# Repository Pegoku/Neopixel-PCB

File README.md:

# Neopixel-PCB
Neopixel matrix PCB made with kicad.

PS: my first PCB

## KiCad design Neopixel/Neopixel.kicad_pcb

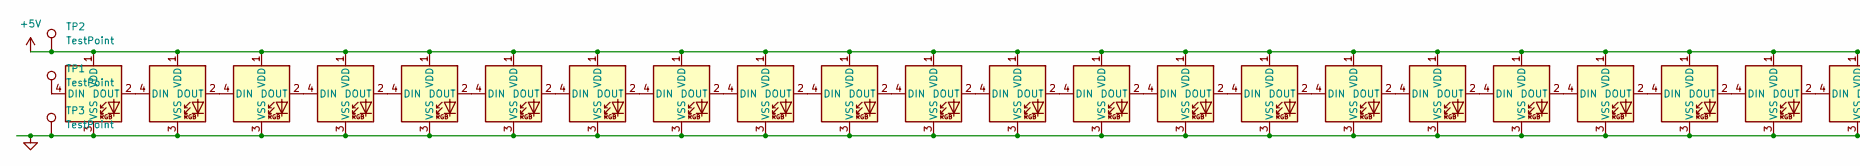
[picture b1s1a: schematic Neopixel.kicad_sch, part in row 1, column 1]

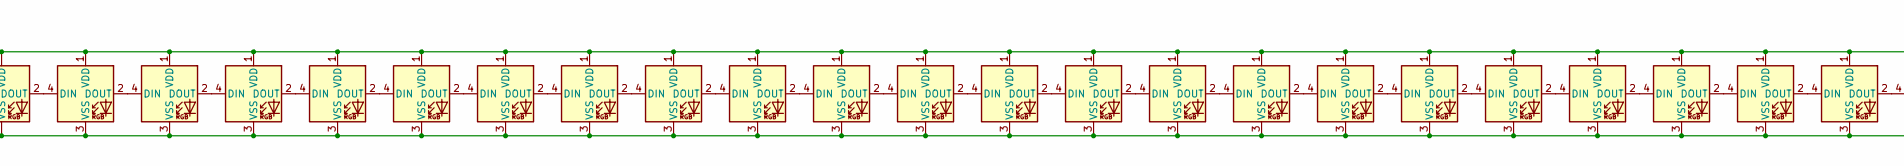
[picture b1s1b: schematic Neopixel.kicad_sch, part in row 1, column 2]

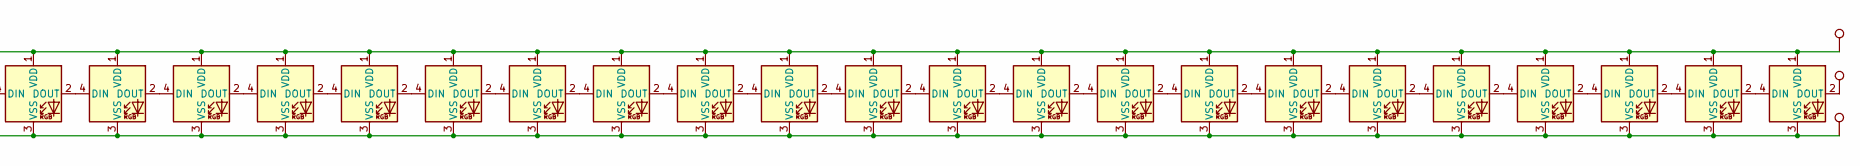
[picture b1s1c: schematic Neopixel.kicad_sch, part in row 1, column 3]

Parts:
D1, D2, D3, D4, D5, D6, D7, D8, D9, D10, D11, D12, D13, D14, D15, D16, D17, D18, D19, D20, D21, D22, D23, D24, D25, D26, D27, D28, D29, D30, D31, D32, D33, D34, D35, D36, D37, D38, D39, D40, D41, D42, D43, D44, D45, D46, D47, D48, D49, D50, D51, D52, D53, D54, D55, D56, D57, D58, D59, D60, D61, D62, D63, D64: WS2812B; LED_WS2812B_PLCC4_5.0x5.0mm_P3.2mm
TP1, TP2, TP3, TP4, TP5, TP6: TestPoint

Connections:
+5V: D1.1 (VDD), D2.1 (VDD), D3.1 (VDD), D4.1 (VDD), D5.1 (VDD), D6.1 (VDD), D7.1 (VDD), D8.1 (VDD), D9.1 (VDD), D10.1 (VDD), D11.1 (VDD), D12.1 (VDD), D13.1 (VDD), D14.1 (VDD), D15.1 (VDD), D16.1 (VDD), D17.1 (VDD), D18.1 (VDD), D19.1 (VDD), D20.1 (VDD), D21.1 (VDD), D22.1 (VDD), D23.1 (VDD), D24.1 (VDD), D25.1 (VDD), D26.1 (VDD), D27.1 (VDD), D28.1 (VDD), D29.1 (VDD), D30.1 (VDD), D31.1 (VDD), D32.1 (VDD), D33.1 (VDD), D34.1 (VDD), D35.1 (VDD), D36.1 (VDD), D37.1 (VDD), D38.1 (VDD), D39.1 (VDD), D40.1 (VDD), D41.1 (VDD), D42.1 (VDD), D43.1 (VDD), D44.1 (VDD), D45.1 (VDD), D46.1 (VDD), D47.1 (VDD), D48.1 (VDD), D49.1 (VDD), D50.1 (VDD), D51.1 (VDD), D52.1 (VDD), D53.1 (VDD), D54.1 (VDD), D55.1 (VDD), D56.1 (VDD), D57.1 (VDD), D58.1 (VDD), D59.1 (VDD), D60.1 (VDD), D61.1 (VDD), D62.1 (VDD), D63.1 (VDD), D64.1 (VDD), TP2.1, TP5.1; also elsewhere on the board
GND: D1.3 (VSS), D2.3 (VSS), D3.3 (VSS), D4.3 (VSS), D5.3 (VSS), D6.3 (VSS), D7.3 (VSS), D8.3 (VSS), D9.3 (VSS), D10.3 (VSS), D11.3 (VSS), D12.3 (VSS), D13.3 (VSS), D14.3 (VSS), D15.3 (VSS), D16.3 (VSS), D17.3 (VSS), D18.3 (VSS), D19.3 (VSS), D20.3 (VSS), D21.3 (VSS), D22.3 (VSS), D23.3 (VSS), D24.3 (VSS), D25.3 (VSS), D26.3 (VSS), D27.3 (VSS), D28.3 (VSS), D29.3 (VSS), D30.3 (VSS), D31.3 (VSS), D32.3 (VSS), D33.3 (VSS), D34.3 (VSS), D35.3 (VSS), D36.3 (VSS), D37.3 (VSS), D38.3 (VSS), D39.3 (VSS), D40.3 (VSS), D41.3 (VSS), D42.3 (VSS), D43.3 (VSS), D44.3 (VSS), D45.3 (VSS), D46.3 (VSS), D47.3 (VSS), D48.3 (VSS), D49.3 (VSS), D50.3 (VSS), D51.3 (VSS), D52.3 (VSS), D53.3 (VSS), D54.3 (VSS), D55.3 (VSS), D56.3 (VSS), D57.3 (VSS), D58.3 (VSS), D59.3 (VSS), D60.3 (VSS), D61.3 (VSS), D62.3 (VSS), D63.3 (VSS), D64.3 (VSS), TP3.1, TP4.1; also elsewhere on the board
unnamed 2: D1.4 (DIN), TP1.1; also elsewhere on the board
unnamed: D1.2 (DOUT), D2.4 (DIN)
unnamed: D2.2 (DOUT), D3.4 (DIN)
unnamed: D3.2 (DOUT), D4.4 (DIN)
unnamed: D4.2 (DOUT), D5.4 (DIN)
unnamed: D5.2 (DOUT), D6.4 (DIN)
unnamed: D6.2 (DOUT), D7.4 (DIN)
unnamed: D7.2 (DOUT), D8.4 (DIN)
unnamed: D8.2 (DOUT), D9.4 (DIN)
unnamed: D9.2 (DOUT), D10.4 (DIN)
unnamed: D10.2 (DOUT), D11.4 (DIN)
unnamed: D11.2 (DOUT), D12.4 (DIN)
unnamed: D12.2 (DOUT), D13.4 (DIN)
unnamed: D13.2 (DOUT), D14.4 (DIN)
unnamed: D14.2 (DOUT), D15.4 (DIN)
unnamed: D15.2 (DOUT), D16.4 (DIN)
unnamed: D16.2 (DOUT), D17.4 (DIN)
unnamed: D17.2 (DOUT), D18.4 (DIN)
unnamed: D18.2 (DOUT), D19.4 (DIN)
unnamed: D19.2 (DOUT), D20.4 (DIN)
unnamed: D20.2 (DOUT), D21.4 (DIN)
unnamed: D21.2 (DOUT), D22.4 (DIN)
unnamed: D22.2 (DOUT), D23.4 (DIN)
unnamed: D23.2 (DOUT), D24.4 (DIN)
unnamed: D24.2 (DOUT), D25.4 (DIN)
unnamed: D25.2 (DOUT), D26.4 (DIN)
unnamed: D26.2 (DOUT), D27.4 (DIN)
unnamed: D27.2 (DOUT), D28.4 (DIN)
unnamed: D28.2 (DOUT), D29.4 (DIN)
unnamed: D29.2 (DOUT), D30.4 (DIN)
unnamed: D30.2 (DOUT), D31.4 (DIN)
unnamed: D31.2 (DOUT), D32.4 (DIN)
unnamed: D32.2 (DOUT), D33.4 (DIN)
unnamed: D33.2 (DOUT), D34.4 (DIN)
unnamed: D34.2 (DOUT), D35.4 (DIN)
unnamed: D35.2 (DOUT), D36.4 (DIN)
unnamed: D36.2 (DOUT), D37.4 (DIN)
unnamed: D37.2 (DOUT), D38.4 (DIN)
unnamed: D38.2 (DOUT), D39.4 (DIN)
unnamed: D39.2 (DOUT), D40.4 (DIN)
unnamed: D40.2 (DOUT), D41.4 (DIN)
unnamed: D41.2 (DOUT), D42.4 (DIN)
unnamed: D42.2 (DOUT), D43.4 (DIN)
unnamed: D43.2 (DOUT), D44.4 (DIN)
unnamed: D44.2 (DOUT), D45.4 (DIN)
unnamed: D45.2 (DOUT), D46.4 (DIN)
unnamed: D46.2 (DOUT), D47.4 (DIN)
unnamed: D47.2 (DOUT), D48.4 (DIN)
unnamed: D48.2 (DOUT), D49.4 (DIN)
unnamed: D49.2 (DOUT), D50.4 (DIN)
unnamed: D50.2 (DOUT), D51.4 (DIN)
unnamed: D51.2 (DOUT), D52.4 (DIN)
unnamed: D52.2 (DOUT), D53.4 (DIN)
unnamed: D53.2 (DOUT), D54.4 (DIN)
unnamed: D54.2 (DOUT), D55.4 (DIN)
unnamed: D55.2 (DOUT), D56.4 (DIN)
unnamed: D56.2 (DOUT), D57.4 (DIN)
unnamed: D57.2 (DOUT), D58.4 (DIN)
unnamed: D58.2 (DOUT), D59.4 (DIN)
unnamed: D59.2 (DOUT), D60.4 (DIN)
unnamed: D60.2 (DOUT), D61.4 (DIN)
unnamed: D61.2 (DOUT), D62.4 (DIN)
unnamed: D62.2 (DOUT), D63.4 (DIN)
unnamed: D63.2 (DOUT), D64.4 (DIN)
unnamed 66: D64.2 (DOUT), TP6.1; also elsewhere on the board

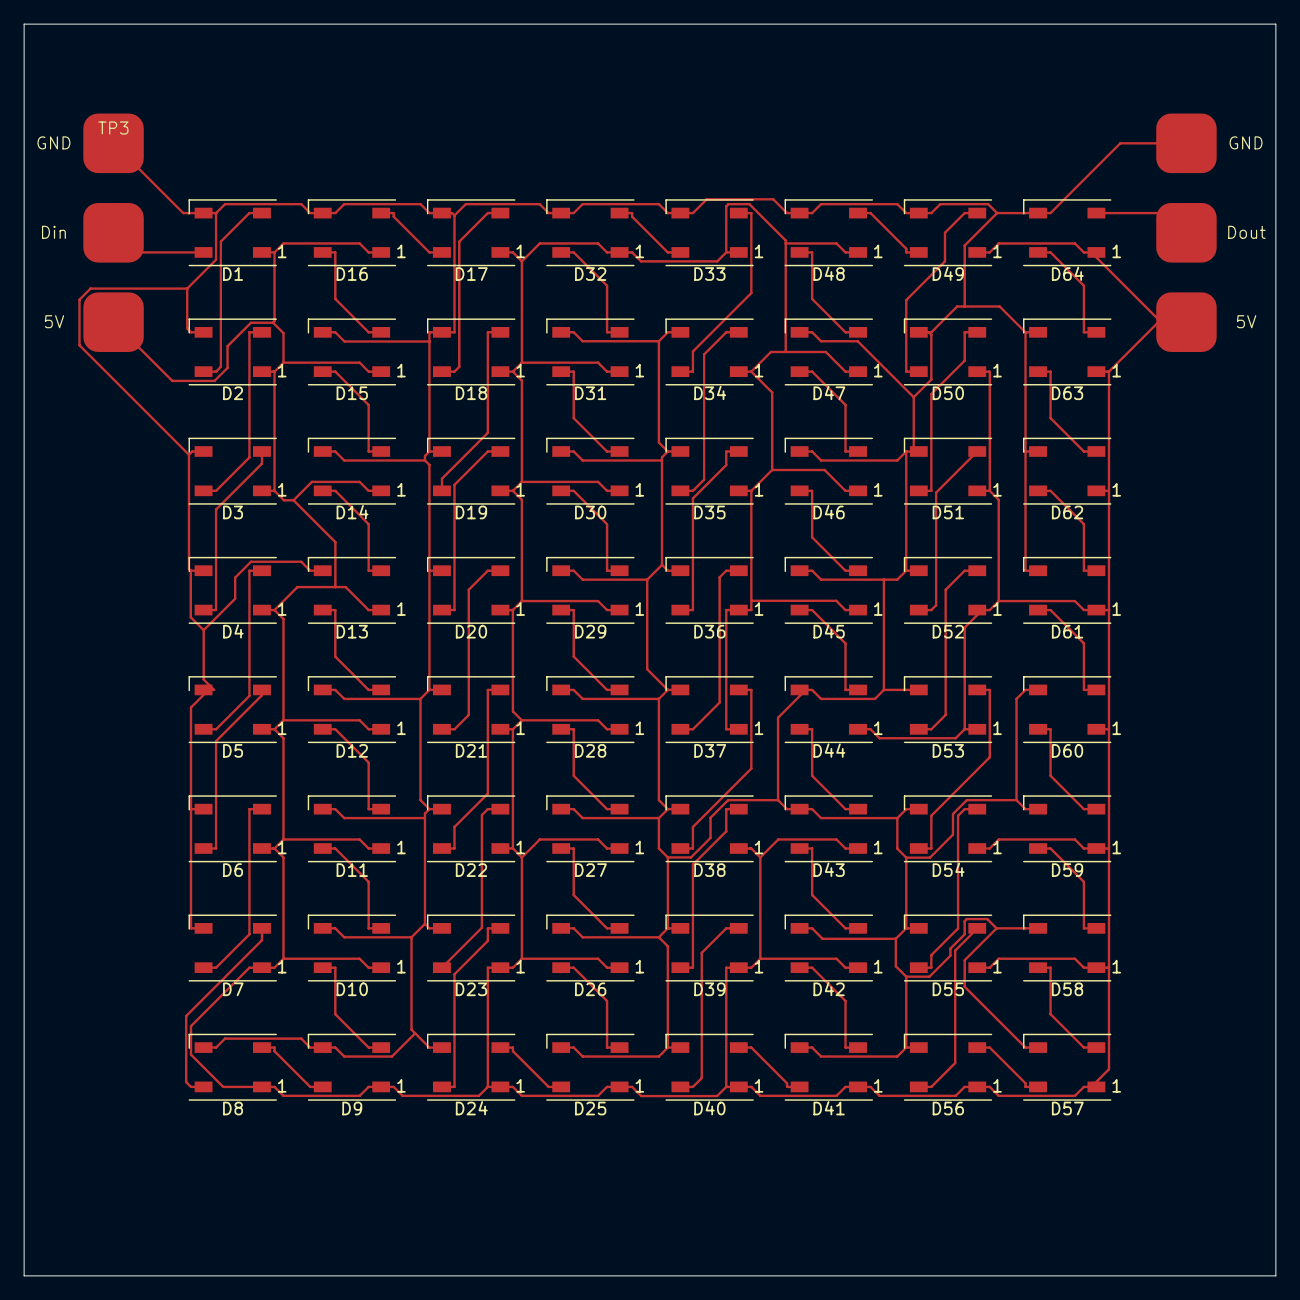
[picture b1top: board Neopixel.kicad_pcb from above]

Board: 2 copper layers, 105.0 x 105.0 mm, 70 parts (0 on the bottom side), 67 nets.

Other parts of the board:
5V, 5V#2: TestPoint
Din: TestPoint
Dout: TestPoint
GND: TestPoint

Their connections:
+5V: 5V.1, 5V#2.1; also elsewhere on the board
GND: GND.1; also elsewhere on the board
unnamed 2: Din.1; also elsewhere on the board
unnamed 66: Dout.1; also elsewhere on the board

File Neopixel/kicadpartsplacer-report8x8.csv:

ref des,value,Package,x,y,rotation,side,show ref des,show value
D1,WS2812B,LED_SMD:LED_WS2812B_PLCC4_5.0x5.0mm_P3.2mm,25,-25,180,front,1,1
D2,WS2812B,LED_SMD:LED_WS2812B_PLCC4_5.0x5.0mm_P3.2mm,25,-35,180,front,1,1
D3,WS2812B,LED_SMD:LED_WS2812B_PLCC4_5.0x5.0mm_P3.2mm,25,-45,180,front,1,1
D4,WS2812B,LED_SMD:LED_WS2812B_PLCC4_5.0x5.0mm_P3.2mm,25,-55,180,front,1,1
D5,WS2812B,LED_SMD:LED_WS2812B_PLCC4_5.0x5.0mm_P3.2mm,25,-65,180,front,1,1
D6,WS2812B,LED_SMD:LED_WS2812B_PLCC4_5.0x5.0mm_P3.2mm,25,-75,180,front,1,1
D7,WS2812B,LED_SMD:LED_WS2812B_PLCC4_5.0x5.0mm_P3.2mm,25,-85,180,front,1,1
D8,WS2812B,LED_SMD:LED_WS2812B_PLCC4_5.0x5.0mm_P3.2mm,25,-95,180,front,1,1
D9,WS2812B,LED_SMD:LED_WS2812B_PLCC4_5.0x5.0mm_P3.2mm,35,-95,180,front,1,1
D10,WS2812B,LED_SMD:LED_WS2812B_PLCC4_5.0x5.0mm_P3.2mm,35,-85,180,front,1,1
D11,WS2812B,LED_SMD:LED_WS2812B_PLCC4_5.0x5.0mm_P3.2mm,35,-75,180,front,1,1
D12,WS2812B,LED_SMD:LED_WS2812B_PLCC4_5.0x5.0mm_P3.2mm,35,-65,180,front,1,1
D13,WS2812B,LED_SMD:LED_WS2812B_PLCC4_5.0x5.0mm_P3.2mm,35,-55,180,front,1,1
D14,WS2812B,LED_SMD:LED_WS2812B_PLCC4_5.0x5.0mm_P3.2mm,35,-45,180,front,1,1
D15,WS2812B,LED_SMD:LED_WS2812B_PLCC4_5.0x5.0mm_P3.2mm,35,-35,180,front,1,1
D16,WS2812B,LED_SMD:LED_WS2812B_PLCC4_5.0x5.0mm_P3.2mm,35,-25,180,front,1,1
D17,WS2812B,LED_SMD:LED_WS2812B_PLCC4_5.0x5.0mm_P3.2mm,45,-25,180,front,1,1
D18,WS2812B,LED_SMD:LED_WS2812B_PLCC4_5.0x5.0mm_P3.2mm,45,-35,180,front,1,1
D19,WS2812B,LED_SMD:LED_WS2812B_PLCC4_5.0x5.0mm_P3.2mm,45,-45,180,front,1,1
D20,WS2812B,LED_SMD:LED_WS2812B_PLCC4_5.0x5.0mm_P3.2mm,45,-55,180,front,1,1
D21,WS2812B,LED_SMD:LED_WS2812B_PLCC4_5.0x5.0mm_P3.2mm,45,-65,180,front,1,1
D22,WS2812B,LED_SMD:LED_WS2812B_PLCC4_5.0x5.0mm_P3.2mm,45,-75,180,front,1,1
D23,WS2812B,LED_SMD:LED_WS2812B_PLCC4_5.0x5.0mm_P3.2mm,45,-85,180,front,1,1
D24,WS2812B,LED_SMD:LED_WS2812B_PLCC4_5.0x5.0mm_P3.2mm,45,-95,180,front,1,1
D25,WS2812B,LED_SMD:LED_WS2812B_PLCC4_5.0x5.0mm_P3.2mm,55,-95,180,front,1,1
D26,WS2812B,LED_SMD:LED_WS2812B_PLCC4_5.0x5.0mm_P3.2mm,55,-85,180,front,1,1
D27,WS2812B,LED_SMD:LED_WS2812B_PLCC4_5.0x5.0mm_P3.2mm,55,-75,180,front,1,1
D28,WS2812B,LED_SMD:LED_WS2812B_PLCC4_5.0x5.0mm_P3.2mm,55,-65,180,front,1,1
D29,WS2812B,LED_SMD:LED_WS2812B_PLCC4_5.0x5.0mm_P3.2mm,55,-55,180,front,1,1
D30,WS2812B,LED_SMD:LED_WS2812B_PLCC4_5.0x5.0mm_P3.2mm,55,-45,180,front,1,1
D31,WS2812B,LED_SMD:LED_WS2812B_PLCC4_5.0x5.0mm_P3.2mm,55,-35,180,front,1,1
D32,WS2812B,LED_SMD:LED_WS2812B_PLCC4_5.0x5.0mm_P3.2mm,55,-25,180,front,1,1
D33,WS2812B,LED_SMD:LED_WS2812B_PLCC4_5.0x5.0mm_P3.2mm,65,-25,180,front,1,1
D34,WS2812B,LED_SMD:LED_WS2812B_PLCC4_5.0x5.0mm_P3.2mm,65,-35,180,front,1,1
D35,WS2812B,LED_SMD:LED_WS2812B_PLCC4_5.0x5.0mm_P3.2mm,65,-45,180,front,1,1
D36,WS2812B,LED_SMD:LED_WS2812B_PLCC4_5.0x5.0mm_P3.2mm,65,-55,180,front,1,1
D37,WS2812B,LED_SMD:LED_WS2812B_PLCC4_5.0x5.0mm_P3.2mm,65,-65,180,front,1,1
D38,WS2812B,LED_SMD:LED_WS2812B_PLCC4_5.0x5.0mm_P3.2mm,65,-75,180,front,1,1
D39,WS2812B,LED_SMD:LED_WS2812B_PLCC4_5.0x5.0mm_P3.2mm,65,-85,180,front,1,1
D40,WS2812B,LED_SMD:LED_WS2812B_PLCC4_5.0x5.0mm_P3.2mm,65,-95,180,front,1,1
D41,WS2812B,LED_SMD:LED_WS2812B_PLCC4_5.0x5.0mm_P3.2mm,75,-95,180,front,1,1
D42,WS2812B,LED_SMD:LED_WS2812B_PLCC4_5.0x5.0mm_P3.2mm,75,-85,180,front,1,1
D43,WS2812B,LED_SMD:LED_WS2812B_PLCC4_5.0x5.0mm_P3.2mm,75,-75,180,front,1,1
D44,WS2812B,LED_SMD:LED_WS2812B_PLCC4_5.0x5.0mm_P3.2mm,75,-65,180,front,1,1
D45,WS2812B,LED_SMD:LED_WS2812B_PLCC4_5.0x5.0mm_P3.2mm,75,-55,180,front,1,1
D46,WS2812B,LED_SMD:LED_WS2812B_PLCC4_5.0x5.0mm_P3.2mm,75,-45,180,front,1,1
D47,WS2812B,LED_SMD:LED_WS2812B_PLCC4_5.0x5.0mm_P3.2mm,75,-35,180,front,1,1
D48,WS2812B,LED_SMD:LED_WS2812B_PLCC4_5.0x5.0mm_P3.2mm,75,-25,180,front,1,1
D49,WS2812B,LED_SMD:LED_WS2812B_PLCC4_5.0x5.0mm_P3.2mm,85,-25,180,front,1,1
D50,WS2812B,LED_SMD:LED_WS2812B_PLCC4_5.0x5.0mm_P3.2mm,85,-35,180,front,1,1
D51,WS2812B,LED_SMD:LED_WS2812B_PLCC4_5.0x5.0mm_P3.2mm,85,-45,180,front,1,1
D52,WS2812B,LED_SMD:LED_WS2812B_PLCC4_5.0x5.0mm_P3.2mm,85,-55,180,front,1,1
D53,WS2812B,LED_SMD:LED_WS2812B_PLCC4_5.0x5.0mm_P3.2mm,85,-65,180,front,1,1
D54,WS2812B,LED_SMD:LED_WS2812B_PLCC4_5.0x5.0mm_P3.2mm,85,-75,180,front,1,1
D55,WS2812B,LED_SMD:LED_WS2812B_PLCC4_5.0x5.0mm_P3.2mm,85,-85,180,front,1,1
D56,WS2812B,LED_SMD:LED_WS2812B_PLCC4_5.0x5.0mm_P3.2mm,85,-95,180,front,1,1
D57,WS2812B,LED_SMD:LED_WS2812B_PLCC4_5.0x5.0mm_P3.2mm,95,-95,180,front,1,1
D58,WS2812B,LED_SMD:LED_WS2812B_PLCC4_5.0x5.0mm_P3.2mm,95,-85,180,front,1,1
D59,WS2812B,LED_SMD:LED_WS2812B_PLCC4_5.0x5.0mm_P3.2mm,95,-75,180,front,1,1
D60,WS2812B,LED_SMD:LED_WS2812B_PLCC4_5.0x5.0mm_P3.2mm,95,-65,180,front,1,1
D61,WS2812B,LED_SMD:LED_WS2812B_PLCC4_5.0x5.0mm_P3.2mm,95,-55,180,front,1,1
D62,WS2812B,LED_SMD:LED_WS2812B_PLCC4_5.0x5.0mm_P3.2mm,95,-45,180,front,1,1
D63,WS2812B,LED_SMD:LED_WS2812B_PLCC4_5.0x5.0mm_P3.2mm,95,-35,180,front,1,1
D64,WS2812B,LED_SMD:LED_WS2812B_PLCC4_5.0x5.0mm_P3.2mm,95,-25,180,front,1,1

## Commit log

2024-08-03 Start
2024-08-03 routed
2024-08-04 designing
2024-08-04 done
2024-08-04 finished
